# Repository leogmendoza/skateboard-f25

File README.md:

# Electrium Mobility F25 Skateboard
This repository contains all the firmware and hardware for Electrium Mobility's F25 Electric Skateboard.

See our project write-up on the [Electrium Mobility website](https://electriummobility.com/docs/F2025-projects/F25%20Skateboard)!

## Projects
- Telemetry
- Power Distribution
- Tail Lights
- Head Lights

## Setup

### Prerequisites
- Git (install and configure with GitHub account)

#### Firmware Subteam
- VS Code
- PlatformIO Extension (on VS Code)

#### Electrical Subteam
- KiCad 9 (latest)

### Clone the Repo
```bash
git clone https://github.com/leogmendoza/skateboard-f25.git
cd skateboard-f25
```

## Contributing

### Firmware Instructions
1. Open VS Code
2. Navigate to your assigned project's `fw` folder (e.g. telemetry):
    ```bash
    cd telemetry/fw
3. Develop, then use PlatformIO tools to compile, run, and view serial output: 
    - Build
    - Upload
    - Monitor

### Electrical Instructions 
1. Open KiCad 9
2. Open `.kicad_pro` file in your assigned project's `hw/<project>` folder (e.g. telemetry):
    ```bash
    telemetry/hw/telemetry/telemetry.kicad_pro
3. Edit schematic or PCB layout

## Git Workflow
1. Before starting development, create a branch for your task:
    ```bash
    git checkout -b <project>-<task>
2. Develop!
3. Stage your changes before committing:
    ```bash
    git add .
4. Make regular commits with clear messages to document changes (e.g. tail lights firmware):
    ```bash
    git commit -m "Defined light controller FSM"
5. Push your local changes to the remote branch:
    ```bash
    git push origin <project>-<task>
6. Open a pull request (PR) on GitHub and wait for it to be reviewed and merged!

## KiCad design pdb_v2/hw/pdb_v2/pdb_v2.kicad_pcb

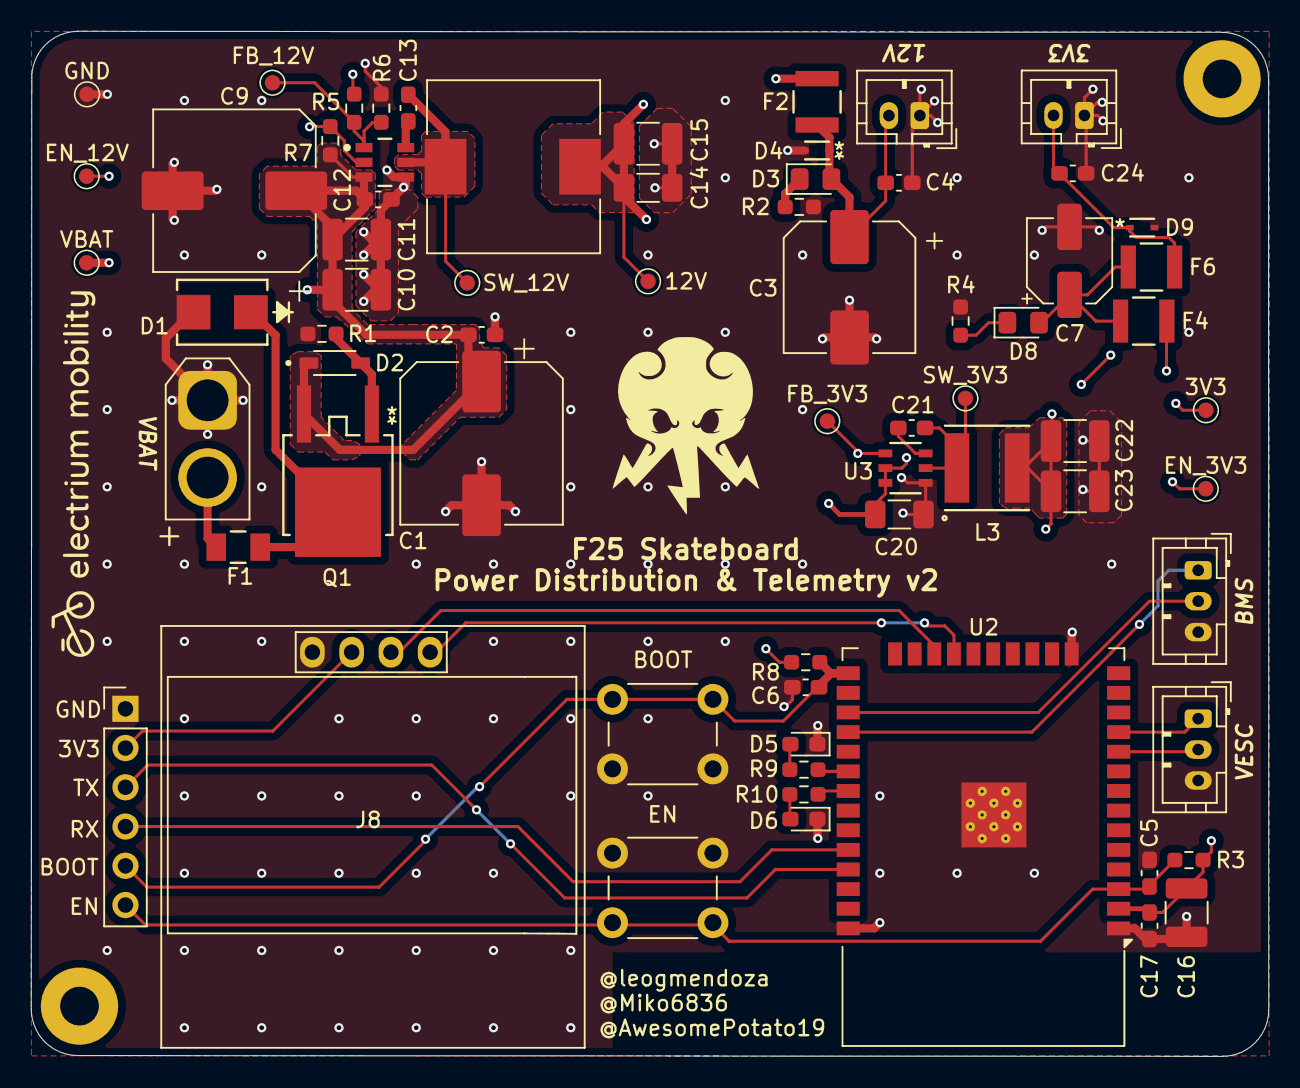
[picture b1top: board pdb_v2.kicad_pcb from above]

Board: 4 copper layers, 80.1 x 66.3 mm, 70 parts (0 on the bottom side), 32 nets.

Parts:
3V3: 3V3; TestPoint_Pad_D1.0mm
12V1: 12V; TestPoint_Pad_D1.0mm
C1: 47uF; CP_Elec_10x10
C2, C4, C5, C6, C12, C13, C17, C21, C24: 0.1uF; C_0603_1608Metric_Pad1.08x0.95mm_HandSolder
C3: 47uF; CP_Elec_8x10
C7: 47uF; CP_Elec_5x5.3
C9: 22uF; CP_Elec_10x10
C10, C11: 2.2uF; C_1210_3225Metric_Pad1.33x2.70mm_HandSolder
C14, C20: 10uF; C_1206_3216Metric_Pad1.33x1.80mm_HandSolder
C15, C16, C22, C23: 22uF; C_1210_3225Metric_Pad1.33x2.70mm_HandSolder
D1: 51Vrwm; SMB_DIO
D2: 15Vz; SOD3715X135N
D3, D8: 2Vf; LED_0805_2012Metric_Pad1.15x1.40mm_HandSolder
D4: 12Vrwm; SOD-523_0P9X1P3_ONS
D5, D6: LED; LED_0603_1608Metric_Pad1.05x0.95mm_HandSolder
D9: 3.3Vrwm; SOD-523_0P9X1P3_ONS
EN_3V3: EN_3V3; TestPoint_Pad_D1.0mm
EN_12V1: EN_12V; TestPoint_Pad_D1.0mm
F1: 3.5A 63V; C1_BEL
F2, F4, F6: 0.5A 16V; 0ZCH_BEL
FB_3V3: FB_3V3; TestPoint_Pad_D1.0mm
FB_12V1: FB_12V; TestPoint_Pad_D1.0mm
GND1: GND; TestPoint_Pad_D1.0mm
H1, H2: MountingHole_Pad; MountingHole_2.5mm_Pad
J1: XT30-M_Ver; AMASS_XT30U-M_1x02_P5.0mm_Vertical
J2, J5: JST-PH_01x02; JST_PH_B2B-PH-K_1x02_P2.00mm_Vertical
J3: Conn_01x06_Pin; PinHeader_1x06_P2.54mm_Vertical
J6, J7: Conn_01x03; JST_PH_B3B-PH-K_1x03_P2.00mm_Vertical
J8: Conn_01x04; 128x64OLED
L1: 51uH; IND_1050P-WE-PD_WRE
L3: 3.9uH; IND_WE-LQS_5020_WRE
Q1: 60Vds; PMOSGDS_TO-252_DPAK_GAS
R1, R7: 100k; R_0603_1608Metric_Pad0.98x0.95mm_HandSolder
R2: 4.7k; R_0603_1608Metric_Pad0.98x0.95mm_HandSolder
R3, R8: 10k; R_0603_1608Metric_Pad0.98x0.95mm_HandSolder
R4: 680; R_0603_1608Metric_Pad0.98x0.95mm_HandSolder
R5: 143k; R_0603_1608Metric_Pad0.98x0.95mm_HandSolder
R6: 10.2k; R_0603_1608Metric_Pad0.98x0.95mm_HandSolder
R9, R10: 1k; R_0603_1608Metric_Pad0.98x0.95mm_HandSolder
SW1, SW2: SW_Push; SW_PUSH_6mm
SW_3V3: SW_3V3; TestPoint_Pad_D1.0mm
SW_12V1: SW_12V; TestPoint_Pad_D1.0mm
U1: LMR51635XFDDCR; DDC0006A-MFG
U2: ESP32-WROOM-32
U3: AP63203WU-7; AP63203WU-7_DIO
VBAT1: VBAT; TestPoint_Pad_D1.0mm

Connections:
3V3_BUS: 3V3.1, C16.1, C17.1, C22.1, C23.1, F4.2, FB_3V3.1, J3.2, J8.2, L3.2, R3.1, R8.1, U2.2 (VDD), U3.1 (FB)
12V_BUS: 12V1.1, C14.1, C15.1, C20.1, EN_3V3.1, F2.2, L1.2, R5.1, U3.2 (EN), U3.3 (VIN)
/3V3_SPLIT: C7.1, D8.2 (A), F4.1, F6.2
/BMS RX: J6.2, U2.27 (IO16)
/BMS TX: J6.1, U2.28 (IO17)
/BOOT: C6.1, J3.5, R8.2, SW2.2, U2.25 (IO0)
/EN: C5.1, J3.6, R3.2, SW1.2, U2.3 (EN)
/LED: R9.1, U2.30 (IO18)
/OLED SCL: J8.3, U2.22 (SDI/SD1)
/OLED SDA: J8.4, U2.21 (SDO/SD0)
/RX: J3.4, U2.34 (RXD0/IO3)
/TX: J3.3, U2.35 (TXD0/IO1)
/VESC RX: J7.2, U2.10 (IO25)
/VESC TX: J7.1, U2.11 (IO26)
GND: C1.2, C2.2, C3.2, C4.2, C5.2, C6.2, C7.2, C9.2, C10.2, C11.2, C12.2, C14.2, C15.2, C16.2, C17.2, C20.2, C22.2, C23.2, C24.2, D1.2, D4.2, D5.1 (K), D6.1 (K), D9.2, GND1.1, J1.1, J2.1, J3.1, J5.1, J6.3, J7.3, J8.1, R1.2, R2.1, R4.1, R6.2, SW1.1, SW2.1, U1.4 (GND), U2.1 (GND), U2.15 (GND), U2.38 (GND), U2.39 (GND), U3.4 (GND)
unnamed: D2.2 (A), Q1.1 (G), R1.1
unnamed: C3.1, C4.1, D3.2 (A), D4.1, F2.1, J2.2
unnamed: D3.1 (K), R2.2
unnamed: D5.2 (A), R9.2
unnamed: D6.2 (A), R10.2
unnamed: D8.1 (K), R4.2
unnamed: F1.1, J1.2
unnamed: C24.1, D9.1, F6.1, J5.2
unnamed: D1.1, F1.2, Q1.2 (D)
unnamed: C13.1, U1.6 (CB)
unnamed: EN_12V1.1, R7.1, U1.2 (EN)
unnamed: FB_12V1.1, R5.2, R6.1, U1.1 (FB)
unnamed: C13.2, L1.1, SW_12V1.1, U1.5 (SW)
unnamed: R10.1, U2.31 (IO19)
unnamed: C21.1, U3.6 (BST)
unnamed: C21.2, L3.1, SW_3V3.1, U3.5 (SW)
VBAT: C1.1, C2.1, C9.1, C10.1, C11.1, C12.1, D2.1 (K), Q1.3 (S), R7.2, U1.3 (VIN), VBAT1.1

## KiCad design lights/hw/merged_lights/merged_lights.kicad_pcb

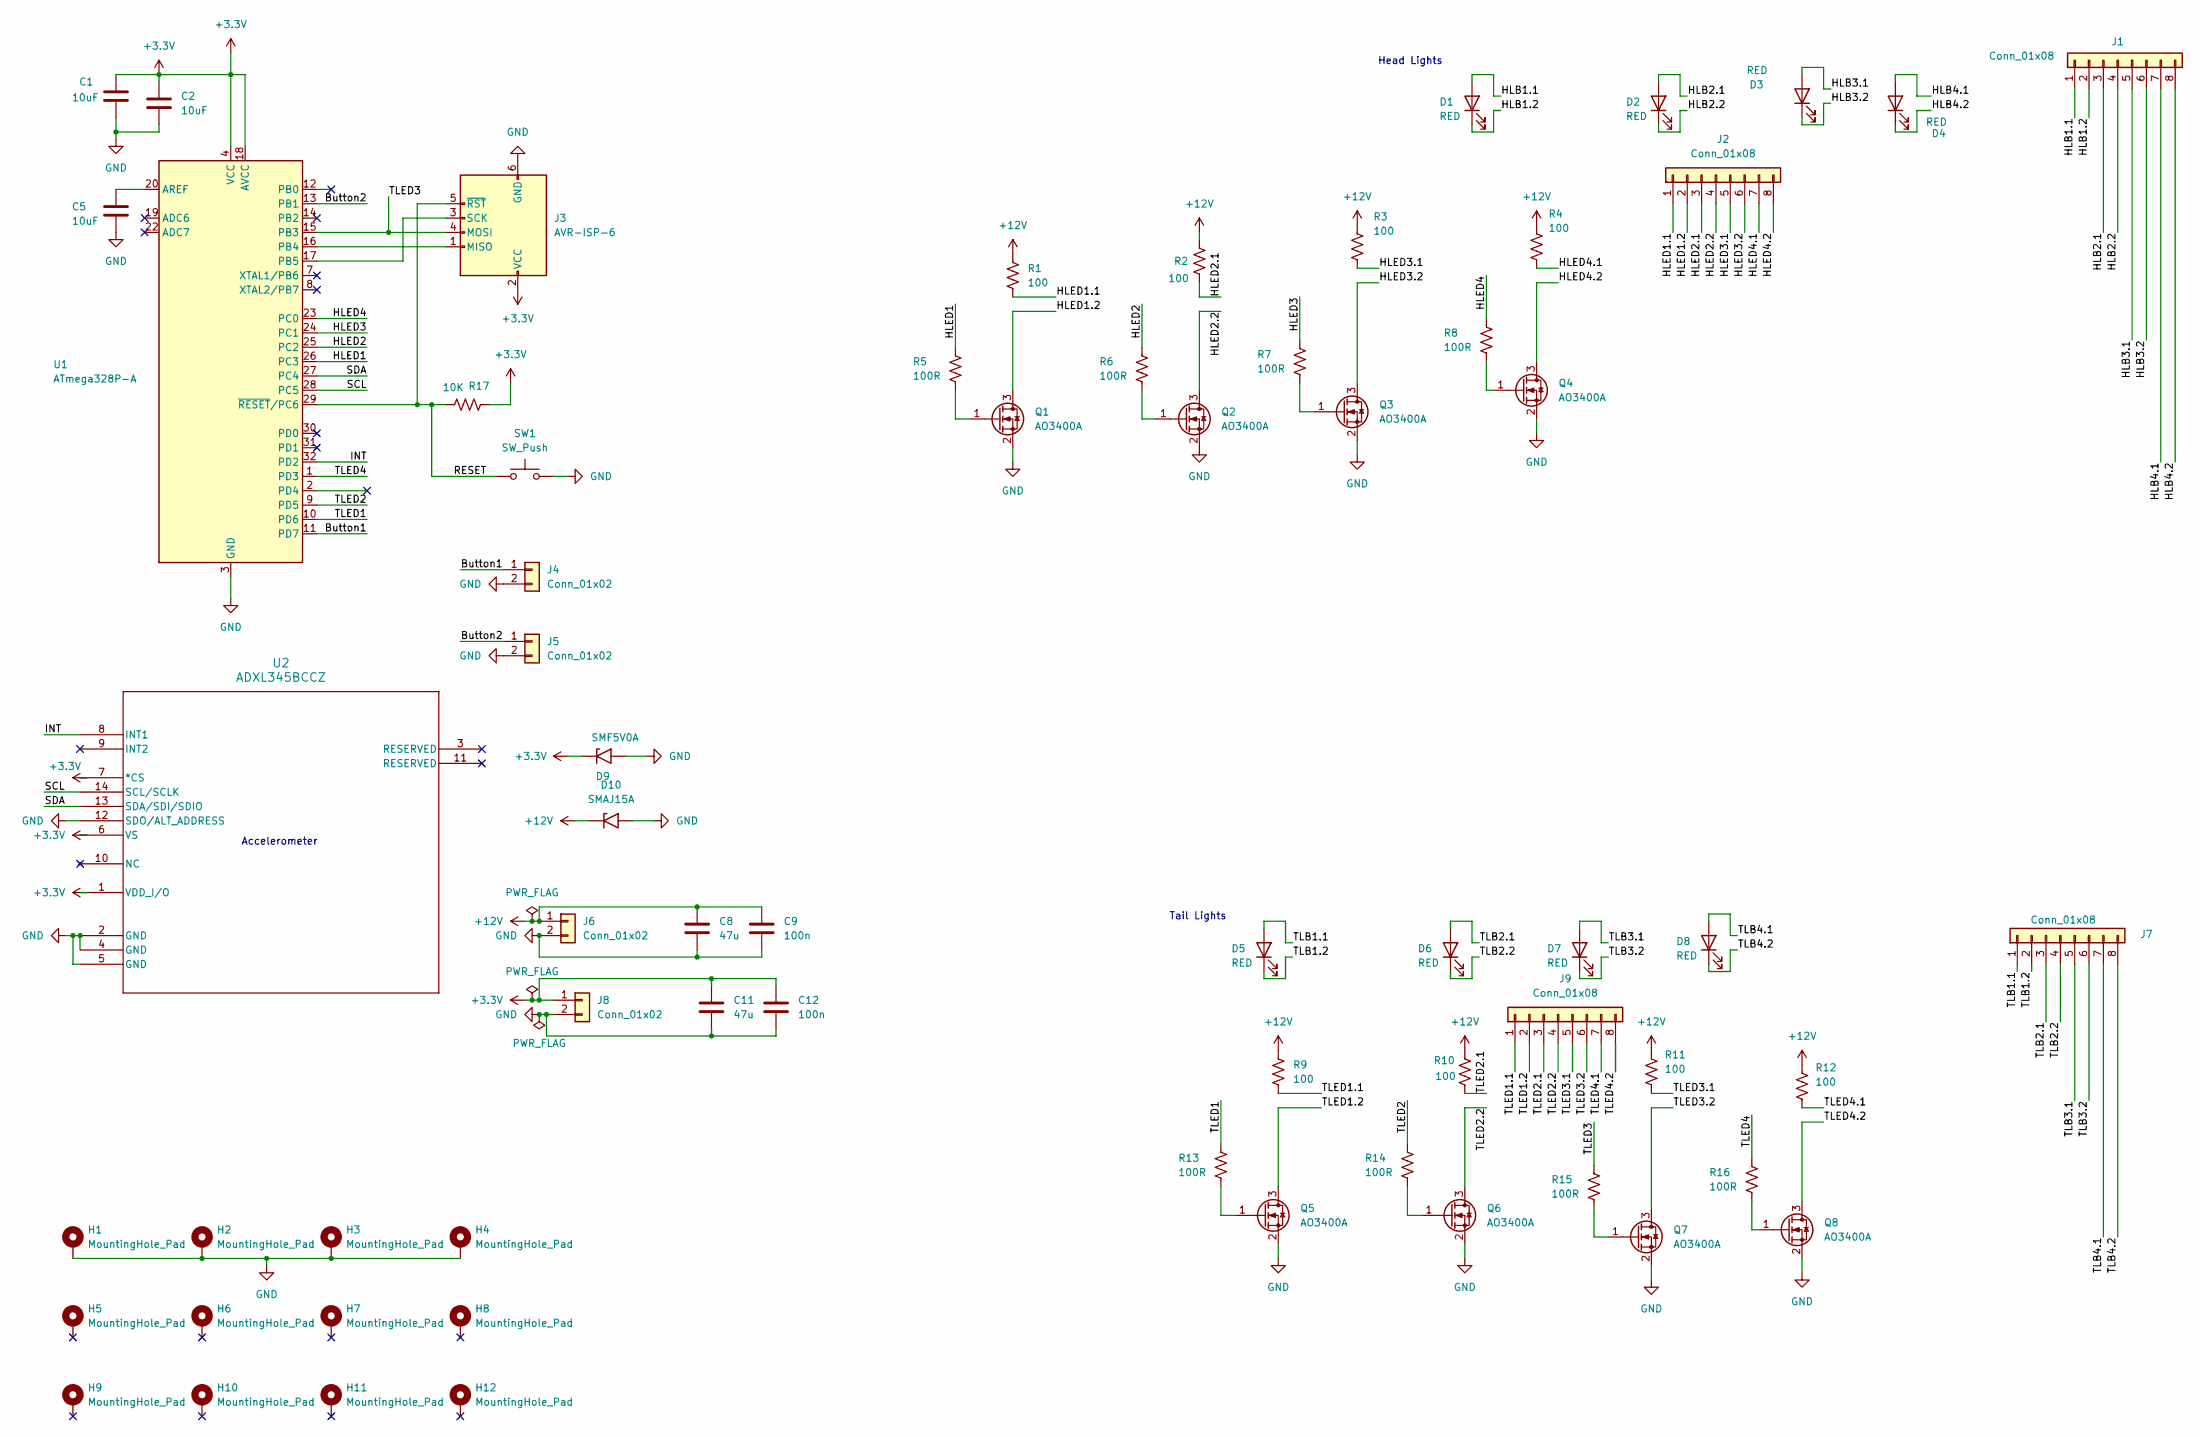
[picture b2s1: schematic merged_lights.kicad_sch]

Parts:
C1, C2, C5: 10uF; C_0805_2012Metric_Pad1.18x1.45mm_HandSolder
C8, C11: 47u; C_0805_2012Metric_Pad1.18x1.45mm_HandSolder
C9, C12: 100n; C_0805_2012Metric_Pad1.18x1.45mm_HandSolder
D1, D2, D3, D4: RED; ABEZD10CA3K65
D5, D6, D7, D8: RED; ABEZD03RA3
D9: SMF5V0A; D_SMF
D10: SMAJ15A; D_SMA
H1, H2, H3, H4: MountingHole_Pad; MountingHole_2.5mm_Pad_Via
H5, H6, H7, H8, H9, H10, H11, H12: MountingHole_Pad; MountingHole_2.5mm_Pad
J1, J2, J7, J9: Conn_01x08; JST_PH_B8B-PH-K_1x08_P2.00mm_Vertical
J3: AVR-ISP-6; PinHeader_1x06_P1.00mm_Vertical
J4, J5, J6, J8: Conn_01x02; JST_PH_B2B-PH-K_1x02_P2.00mm_Vertical
Q1, Q2, Q3, Q4, Q5, Q6, Q7, Q8: AO3400A; SOT-23
R1, R2, R3, R4, R9, R10, R11, R12: 100; R_0805_2012Metric_Pad1.20x1.40mm_HandSolder
R5, R6, R7, R8, R13, R14, R15, R16: 100R; R_0805_2012Metric_Pad1.20x1.40mm_HandSolder
R17: 10K; R_0805_2012Metric_Pad1.20x1.40mm_HandSolder
SW1: SW_Push; SW_PUSH_6mm
U1: ATmega328P-A; TQFP-32_7x7mm_P0.8mm
U2: ADXL345BCCZ; LGA_CC-14-1_ADI

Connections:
+3.3V: C1.1, C2.1, C11.1, C12.1, D9.1 (A1), J3.2 (VCC), J8.1, R17.2, U1.4 (VCC), U1.6 (VCC), U1.18 (AVCC), U2.1 (VDD_I/O), U2.6 (VS), U2.7 (*CS)
+12V: C8.1, C9.1, D10.1 (A1), J6.1, R1.1, R2.1, R3.1, R4.1, R9.1, R10.1, R11.1, R12.1
/Button1: J4.1, U1.11 (PD7)
/Button2: J5.1, U1.13 (PB1)
/HLB1.1: D1.2 (A), J1.1
/HLB1.2: D1.1 (K), J1.2
/HLB2.1: D2.2 (A), J1.3
/HLB2.2: D2.1 (K), J1.4
/HLB3.1: D3.2 (A), J1.5
/HLB3.2: D3.1 (K), J1.6
/HLB4.1: D4.2 (A), J1.7
/HLB4.2: D4.1 (K), J1.8
/HLED1: R5.1, U1.26 (PC3)
/HLED1.1: J2.1, R1.2
/HLED1.2: J2.2, Q1.3 (D)
/HLED2: R6.1, U1.25 (PC2)
/HLED2.1: J2.3, R2.2
/HLED2.2: J2.4, Q2.3 (D)
/HLED3: R7.1, U1.24 (PC1)
/HLED3.1: J2.5, R3.2
/HLED3.2: J2.6, Q3.3 (D)
/HLED4: R8.1, U1.23 (PC0)
/HLED4.1: J2.7, R4.2
/HLED4.2: J2.8, Q4.3 (D)
/INT: U1.32 (PD2), U2.8 (INT1)
/RESET: J3.5 (~RST), R17.1, SW1.1, U1.29 (~RESET/PC6)
/SCL: U1.28 (PC5), U2.14 (SCL/SCLK)
/SDA: U1.27 (PC4), U2.13 (SDA/SDI/SDIO)
/TLB1.1: D5.2 (A), J7.1
/TLB1.2: D5.1 (K), J7.2
/TLB2.1: D6.2 (A), J7.3
/TLB2.2: D6.1 (K), J7.4
/TLB3.1: D7.2 (A), J7.5
/TLB3.2: D7.1 (K), J7.6
/TLB4.1: D8.2 (A), J7.7
/TLB4.2: D8.1 (K), J7.8
/TLED1: R13.1, U1.10 (PD6)
/TLED1.1: J9.1, R9.2
/TLED1.2: J9.2, Q5.3 (D)
/TLED2: R14.1, U1.9 (PD5)
/TLED2.1: J9.3, R10.2
/TLED2.2: J9.4, Q6.3 (D)
/TLED3: J3.4 (MOSI), R15.1, U1.15 (PB3)
/TLED3.1: J9.5, R11.2
/TLED3.2: J9.6, Q7.3 (D)
/TLED4: R16.1, U1.1 (PD3)
/TLED4.1: J9.7, R12.2
/TLED4.2: J9.8, Q8.3 (D)
GND: C1.2, C2.2, C5.2, C8.2, C9.2, C11.2, C12.2, D9.2 (A2), D10.2 (A2), H1.1, H2.1, H3.1, H4.1, J3.6 (GND), J4.2, J5.2, J6.2, J8.2, Q1.2 (S), Q2.2 (S), Q3.2 (S), Q4.2 (S), Q5.2 (S), Q6.2 (S), Q7.2 (S), Q8.2 (S), SW1.2, U1.3 (GND), U1.5 (GND), U1.21 (GND), U2.2 (GND), U2.4 (GND), U2.5 (GND), U2.12 (SDO/ALT_ADDRESS)
unnamed: J3.1 (MISO), U1.16 (PB4)
unnamed: J3.3 (SCK), U1.17 (PB5)
unnamed: Q1.1 (G), R5.2
unnamed: Q2.1 (G), R6.2
unnamed: Q3.1 (G), R7.2
unnamed: Q4.1 (G), R8.2
unnamed: Q5.1 (G), R13.2
unnamed: Q6.1 (G), R14.2
unnamed: Q7.1 (G), R15.2
unnamed: Q8.1 (G), R16.2
unnamed: C5.1, U1.20 (AREF)

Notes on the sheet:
Head Lights
Tail Lights
Accelerometer

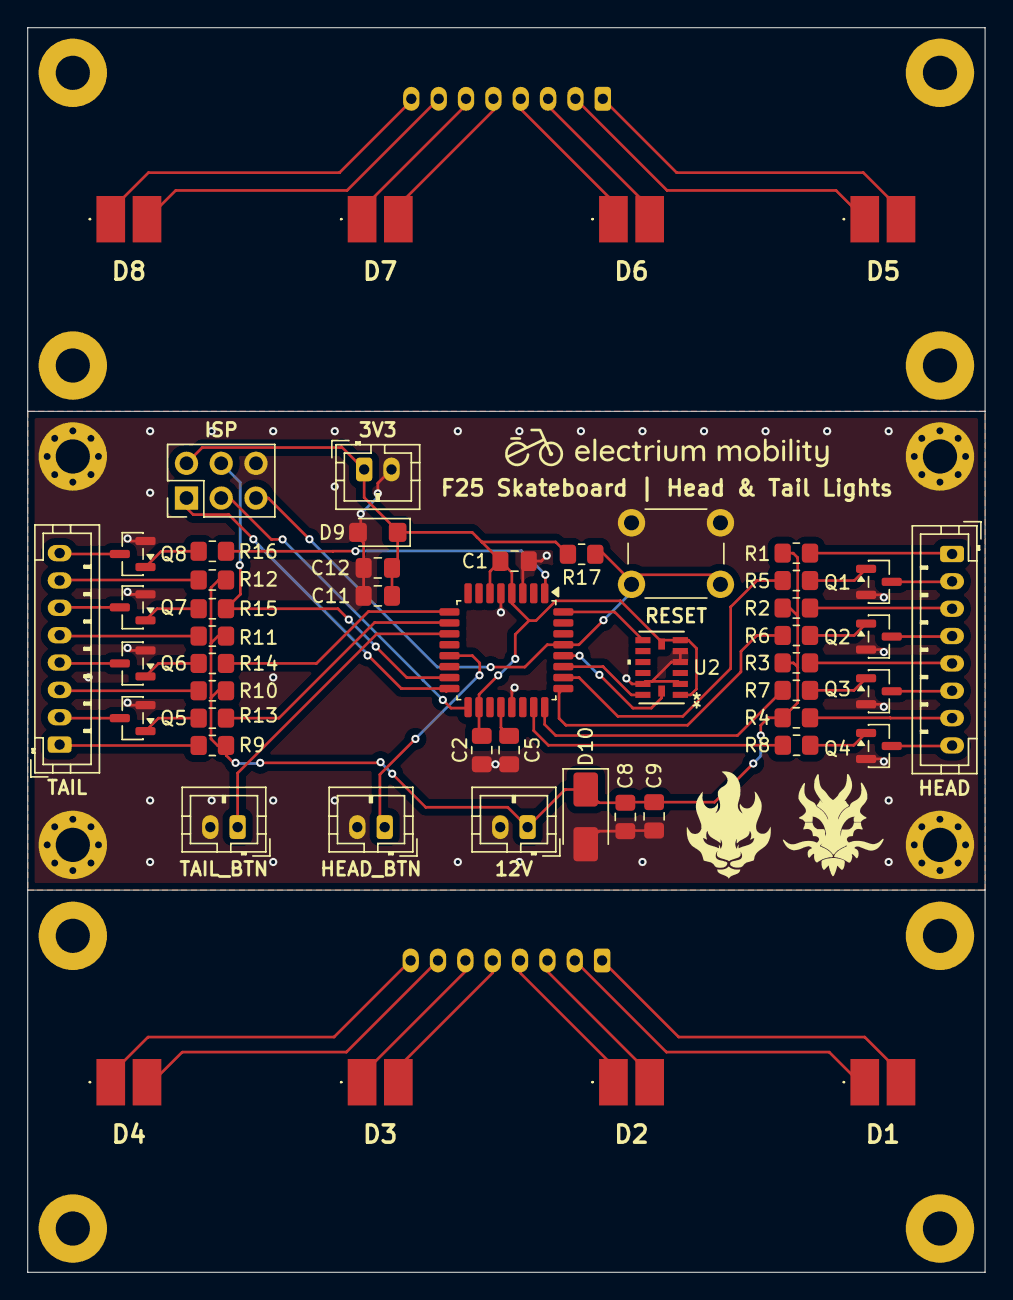
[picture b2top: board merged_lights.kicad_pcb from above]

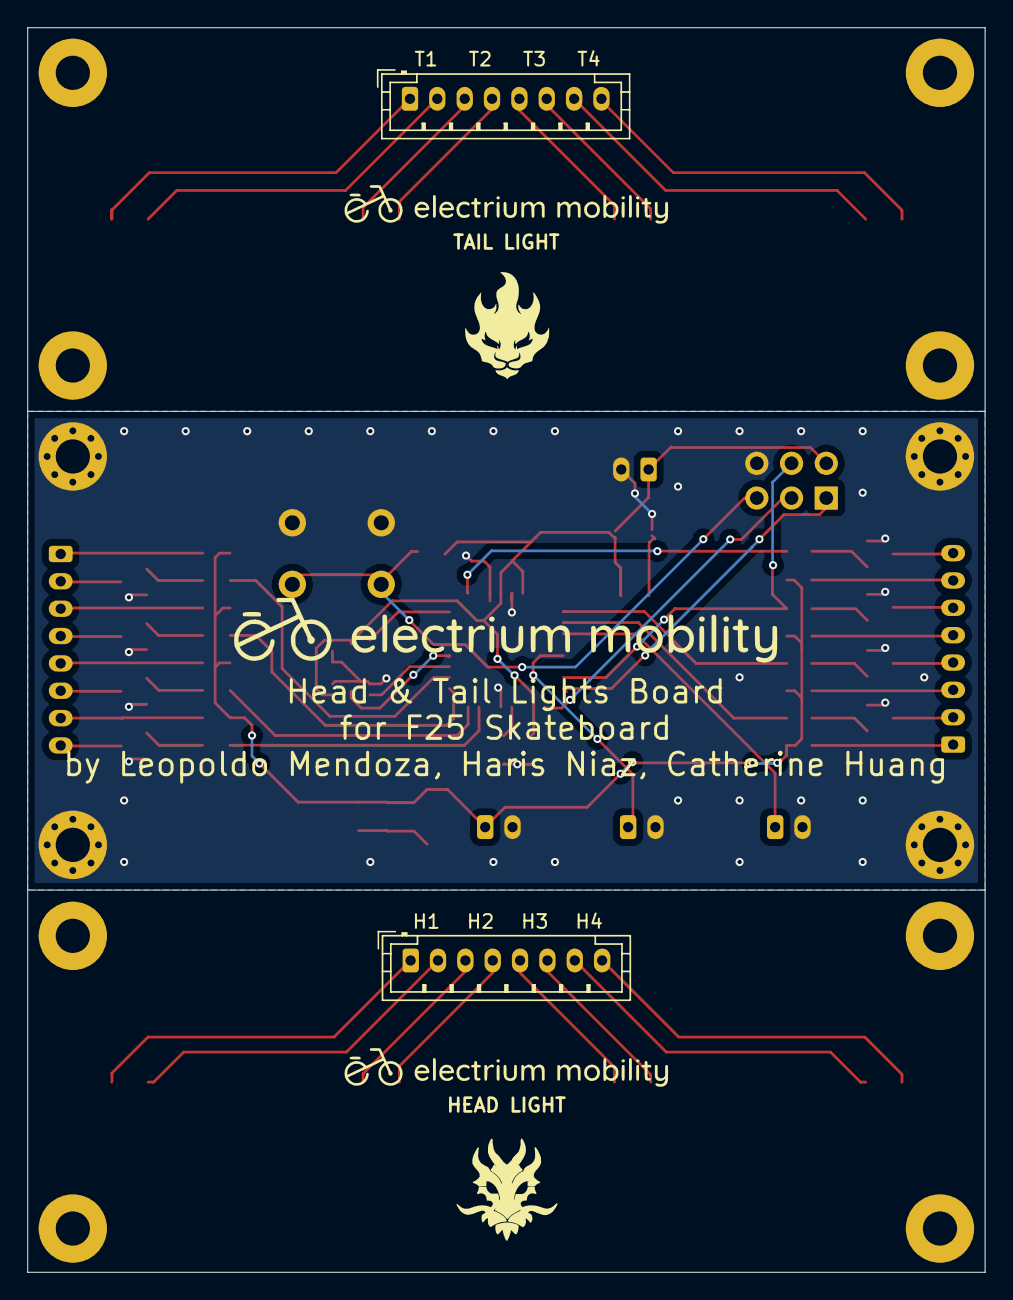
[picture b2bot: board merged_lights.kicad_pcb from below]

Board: 2 copper layers, 70.0 x 91.0 mm, 66 parts (2 on the bottom side), 60 nets.

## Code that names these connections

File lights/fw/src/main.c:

#include <avr/io.h>
#include <avr/interrupt.h>
#include <util/delay.h>

#include "config.h"
#include "utils.h"
#include "i2c.h"
#include "head.h"
#include "tail.h"

#if ENABLE_UART_DEBUG
    #include "uart.h"   
#endif

int main(void) {
    // Note: pins are reverse from main 1x8 to BOTH light boards' 1x8 cuz of crimped wires
    #if ENABLE_PRODUCTION_CODE
        // Initialize GPIO pins of Tail and Head LEDs
        for (uint8_t i = 0; i < NUM_TAIL_LEDS; i++) {
            utils_gpio_set_output(tail_ddr_sequence[i], tail_port_sequence[i], tail_bit_sequence[i]);
        }
        for (uint8_t i = 0; i < NUM_HEAD_LEDS; i++) {
            utils_gpio_set_output(HEAD_LEDS_DDR, HEAD_LEDS_PORT, head_bit_sequence[i]);
        }

        utils_pwm_reset_timers();

        utils_timer1_init();  // Enable timer for system timing

        // Enable timers for PWM
        utils_timer0_init();
        utils_timer2_init();

        i2c_init();  // Enable I2C for accelerometer

        #if ENABLE_UART_DEBUG
            uart_init();
        #endif

        sei();  // Enable global interrupts 

        uint32_t curr_time_ms;
        uint32_t prev_time_ms;

        HeadLight head_light;
        TailLight tail_light;

        head_light_init(&head_light);
        tail_light_init(&tail_light);

        prev_time_ms = utils_uptime_ms();

        while (1) {
            curr_time_ms = utils_uptime_ms();

            if ( (curr_time_ms - prev_time_ms) >= TASK_PERIOD_1000_HZ_IN_MS ) {
                prev_time_ms += TASK_PERIOD_1000_HZ_IN_MS;  // Robust timing

                head_light_update(&head_light);
                tail_light_update(&tail_light);
            }
        }
    #else
        /* ---------- FORCE ALL GATES LOW FIRST ---------- */

        // Tail: clear output latches

        PORTD &= ~((1 << PD6) | (1 << PD5) | (1 << PD3));
        PORTB &= ~(1 << PB3);

        // Head: clear output latches
        PORTC &= ~((1 << PC3) | (1 << PC2) | (1 << PC1) | (1 << PC0));

        // Now configure as outputs
        DDRD |= (1 << PD6) | (1 << PD5) | (1 << PD3);
        DDRB |= (1 << PB3);
        DDRC |= (1 << PC3) | (1 << PC2) | (1 << PC1) | (1 << PC0);

        while (1) {

            /* ---------- ALL ON ---------- */
            PORTD |= (1 << PD6) | (1 << PD5) | (1 << PD3);
            PORTB |= (1 << PB3);

            PORTC |= (1 << PC3) | (1 << PC2) | (1 << PC1) | (1 << PC0);

            _delay_ms(500);

            /* ---------- ALL OFF ---------- */
            PORTD &= ~((1 << PD6) | (1 << PD5) | (1 << PD3));
            PORTB &= ~(1 << PB3);

            PORTC &= ~((1 << PC3) | (1 << PC2) | (1 << PC1) | (1 << PC0));

            _delay_ms(500);
        }
    #endif
}

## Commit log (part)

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2025-09-22 Create CODEOWNERS
2025-09-22 Set up project directories with PlatformIO
2025-09-22 Add setup instructions
2025-09-25 Added blank schematics for KiCad
2025-10-06 Set up sheets and add input stage
2025-10-06 Add telemetry libraries
2025-10-06 Add UART and BLE libraries for telemetry
2025-10-06 Add OLED and accelerometer libraries
2025-10-07 Added telemetry pcb schematic
2025-10-07 Added BMS and battery pack wiring harness schematic
2025-10-08 Added charger port and switch to wiring harness schematic
2025-10-08 Finish Input stage
2025-10-09 Final upload of full KiCad schematic and PCB for headlights
2025-10-09 Finish output stage
2025-10-11 schematic
2025-10-14 Finish stage 1 annotation and stage 2 and 3
2025-10-14 Finished rev 1
2025-10-14 Updated with VESC receiver and button
2025-10-16 Added .kicad_pro file for complete KiCad project access
2025-10-18 Flip LEDs and change RES symbols
2025-10-18 BMS Wiring Harness Schematic (#2)
    * Added BMS and battery pack wiring harness schematic
    * Added charger port and switch to wiring harness schematic
    * Updated with VESC receiver and button
2025-10-18 Added telemetry pcb schematic (#1)
2025-10-20 Remove duplicate KiCad files from repo root and update .kicad_pro
2025-10-20 Headlights schematic update: TVS, caps, AVCC/AREF, R_PHOTO, cleanup
2025-10-22 First PCB draft
2025-10-23 Add test points
2025-10-25 Add mounting holes and refactor test points
2025-10-26 Trace routes
2025-10-27 Finish finding last parts and 3D models
2025-10-27 Add sheet info
2025-11-01 add BmsAPI wrapper
2025-11-02 Add readCells/readTemps APIS (cells via getCells; temps from last status) with fake-mode stubs
2025-11-03 Updated BOM. Ordered parts!
2025-11-04 Add combined lights project
2025-11-04 Copiped pdb_v1 to pdb_v2 for combined PDB and Telemetry PCB
2025-11-04 Added fw folders to new PCB projects
2025-11-05 Removed 12V to 5V stage
2025-11-06 Add stubs for lights FW project
2025-11-07 created BMS wrapper - still need to test
2025-11-08 Update dev envs:
2025-11-08 Blinky!
2025-11-09 Implement lights FSM
2025-11-09 Added telemetry components
2025-11-09 Added footprints
2025-11-09 Add config params
2025-11-10 Create types and function prototypes for utils, led, tail, head
2025-11-10 Refactor fsm
2025-11-10 Add docs to function prototypes
2025-11-10 Ready for task assignment
2025-11-10 Change most inc/ to include/
2025-11-10 added footprints for connectors
2025-11-12 PCB cleaned
2025-11-12 Added lights-backups KiCad folder with latest schematic and PCB files
2025-11-14 Implement Timer1 init
2025-11-14 reverted the platformio file
2025-11-14 renamed the BMS.API file
2025-11-14 made updates with footprints and structure of schematic
2025-11-14 Added lights-backups folder with updated KiCad files
2025-11-15 cleaned up, added oled footprint, arranged some components
2025-11-16 removed second 3v3 connector, arranged telemetry components
2025-11-17 fixed drc errors
2025-11-17 changed the dimensions of L1
2025-11-17 Implement millis() and define Timer1 Compare ISR vector
2025-11-17 added 2 leds on esp32, moved components
2025-11-17 Add telemetry OLED display API and drivers
2025-11-17 changed J1 footprint
2025-11-18 final changes for pcb
2025-11-18 added silkscreen
2025-11-18 changed bom file
2025-11-18 changed silkscreen on back of board
2025-11-19 Layout Update
2025-11-19 aligned mounting holes
2025-11-20 removed diagonal holes
2025-11-20 improved
2025-11-20 ermmm finished Timer0 init??
2025-11-20 committing merged lights
2025-11-20 Unpolished final draft. Need mousebites, proper labelling, etc
2025-11-21 Switching branches
2025-11-21 Still relabeling
2025-11-21 Still relabelling
2025-11-21 Sent to Matthew for review
2025-11-21 Switching
2025-11-21 Add stitching vias
2025-11-21 Zipped up gerber + drill files!
2025-11-21 Exported non-separated gerbers
2025-11-21 sleeping now
2025-11-23 Fix merge conflict with kicad_* files
2025-11-23 Add BmsAPIv1.h header file
2025-11-23 Add BmsAPIv1.cpp file
2025-11-23 Implement timer inits
2025-11-24 Implement duty cycle set and PWM disable
2025-11-24 made esp32 send dummy characteristics to phone every second
2025-11-24 Added files for BLE
2025-11-25 made multiple customizable characteristics to send dummy data to phone every second. added comments
2025-11-26 Set up func prototypes for I2C impl
2025-11-27 Implement I2C init
2025-11-28 Implement start, stop, send addr
2025-11-28 Implepment write, read w/ ack and nack. Ready for higher level abstractions.
2025-11-28 Implement read reg
2025-11-30 Implement multi-read
2025-12-01 Implement accel init
2025-12-01 Implement accel update
2025-12-01 Implement braking funcs
2025-12-01 Implement LEDs
2025-12-01 Implement debouncing
2025-12-01 sending data from the APIs to BLE and OLED
2025-12-01 adjusted the diameter of the wheel for speec clacs
2025-12-11 Switch to Ethan's branch
2025-12-12 Fix compilation errors
2025-12-13 Started to implement tail and head, with changes to the APIs. Might need to refactor some more
2025-12-13 Implement head startup sequence
2025-12-14 Implement head light states
2025-12-14 Fix head lights
2025-12-14 Implement tail lights w/o braking
2025-12-14 Implement simple braking lights
2025-12-14 Implement faded brake lights
2025-12-15 Flashed onto ATMega with ArduinoISP by probing RESET with GND???
2025-12-15 Refactor GPIO to avoid floating MOSFET pins
2026-01-09 Wrap up lights fw
2026-01-09 Wrap up lights FW & HW
2026-01-09 Add vs files to merge lights FW
